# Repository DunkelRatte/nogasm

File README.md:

# Nogasm

This is a fork of the [original nogasm project](https://github.com/nogasm/nogasm).

## Hardware

### Board

Count | Name | Digikey link | Comment |
-----|--------|-------------|---------|
1 | Teensy LC | https://www.digikey.com/short/31cn1n ||
13 | WS2812b RGB LED | https://www.digikey.com/short/31c04r ||
1 | MP3V5050GP | https://www.digikey.com/short/31c04n ||
1 | PEL12T-4225S-S1024 (COM-10982 encoder, backlit) | https://www.digikey.com/short/31cn19 ||
1 | COM-10597 (encoder knob, transparent) | https://www.digikey.com/short/djdq9jpq ||
1 | MCP6001RT-I/OT | https://www.digikey.com/short/31cnvz ||
1 | CGRA4004-G | https://www.digikey.com/short/31c0mw ||
1 | BUK92150-55A | https://www.digikey.com/short/31cnvb ||
3 | MMBT2222A | https://www.digikey.com/short/bmf4f7fn ||
1 | LM7805CT/NOPB | https://www.digikey.com/short/wcn5wvbh | SMD versions more common now |
2 | 10µF 20V tantalum cap 1206 | https://www.digikey.com/short/4pf7p859 || 
15 | 1µF 16V ceramic cap 0805 | https://www.digikey.com/short/31cdcp ||
1 | 0.33µF 16V ceramic cap 0603 | https://www.digikey.com/short/31cdt4 ||
3 | 10nF 16V ceramic cap 0805| https://www.digikey.com/short/31cd7f ||
1 | 10k Ohm trimmer | https://www.digikey.com/short/31cnvv ||
1 | 15k Ohm resistor 0805 | https://www.digikey.com/short/31c04h ||
2 | 10k Ohm resistor 0805 | https://www.digikey.com/short/31cdt9 ||
2 | 750 Ohm resistor 0805 | https://www.digikey.com/short/31cdtw ||
1 | 300 Ohm resistor 0805 | https://www.digikey.com/short/31c04q ||
2 | 180 Ohm resistor 0805 | https://www.digikey.com/short/31cdtn ||
1 | 4pos DIP switch | https://www.digikey.com/short/31cn1m ||
1 | Barreljack socket 1.3mm/3.5mm | https://www.digikey.com/short/31c0mt ||
1 | Barreljack plug 1.3mm/3.5mm | https://www.digikey.com/short/31c0mj ||
1 | Barreljack socket 2.5mm/5.5mm | https://www.digikey.com/short/31c0mh ||

[You can order all of the above parts in one cart from Digikey](https://www.digikey.com/short/d32z5423)

#### Aisler Kit
[You can order PCBs and/or all parts as a single kit on Aisler](https://aisler.net/DunkelRatte/nogasm/board)

#### Power
You'll need 12V/1.5A DC power supply with a 2.5mm/5.5mm barreljack plug (or fitting to above bigger socket).

### Vibrator
The case is designed for a RS-555 motor. [Aliexpress lists several versions](https://www.aliexpress.com/wholesale?SearchText=rs555).
You'll need to press a weight onto it.

Other 12V DC toys controlable with PWM and using up to 2A should work as well.

### Plug
An inflatable buttplug is used for pressure detection. For example "*Fanny Hill*" by *Seven Creations*.

## Software

### Flashing the teensy

[Install the Teensy Loader Application](https://www.pjrc.com/teensy/loader.html).
After There are two ways to get the firmware onto the device:

#### Flashing the compiled .hex
This is the easiest way. Download the `.hex` file and use the loader to upload the file to the device.

#### Compiling the code yourself
[Download and install Teensyduino](https://www.pjrc.com/teensy/td_download.html).
Afterwards get the sourcecode, compile and upload it via the arduino IDE.

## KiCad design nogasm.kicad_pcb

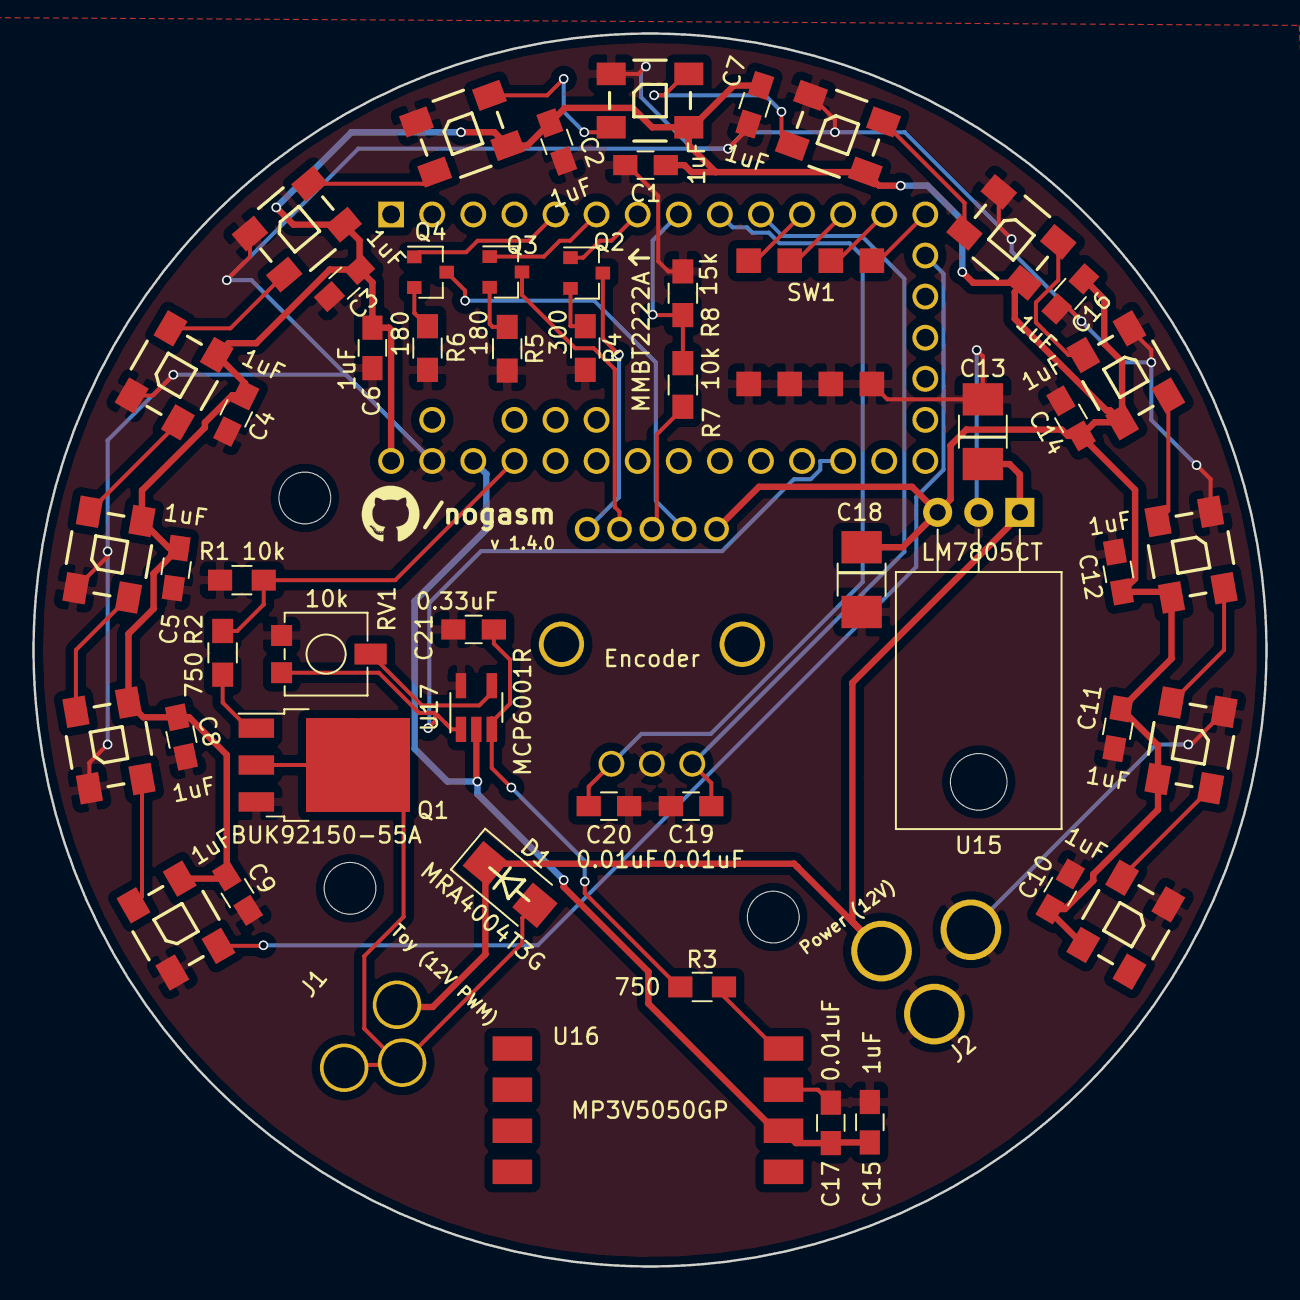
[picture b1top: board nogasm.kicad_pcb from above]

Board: 2 copper layers, 76.2 x 76.2 mm, 56 parts (1 on the bottom side), 41 nets.

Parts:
C1, C2, C3, C4, C5, C6, C7, C8, C9, C10, C11, C12, C14, C15, C16: 1uF; C_0805_HandSoldering
C13, C18: 10uF; C_1210_HandSoldering
C17, C19, C20: 0.01uF; C_0805_HandSoldering
C21: 0.33uF; C_0805_HandSoldering
D1: MRA4004T3G; D_SMA_0202
Encoder: Rotary_Encoder_Switch_RGB; COM-10982
J1: DC Jack PJ-031DH 3.5mm; Barreljack_3mm
J2: DC Jack PRT-10811; Barreljack_5.4mm
Q1: BUK92150-55A; TO-252-3_TabPin2
Q2, Q3, Q4: MMBT2222A; SOT-23
R1, R7: 10k; R_0805_HandSoldering
R2, R3: 750; R_0805_HandSoldering
R4: 300; R_0805_HandSoldering
R5, R6: 180; R_0805_HandSoldering
R8: 15k; R_0805_HandSoldering
RV1: 10k; Potentiometer_Trimmer_Vishay_TS53YL
SW1: SW_DIP_x04; SW_DIP_4_SMD
U1, U2, U3, U4, U5, U6, U7, U8, U9, U10, U11, U12, U13: WS2812B
U14: Teensy-LC; Teensy30_31_32_LC
U15: LM7805CT; TO-220_Horizontal
U16: MP3V5050GP
U17: MCP6001R; SOT-23-5_HandSoldering

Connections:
+3V3: C15.1, C17.1, U14.31, U16.2, U17.2
+5V: C1.1, C2.1, C3.1, C4.1, C5.1, C6.2, C7.1, C8.1, C9.1, C10.1, C11.1, C12.1, C14.1, C16.1, C18.1, Encoder.5, U1.1, U2.1, U3.1, U4.1, U5.1, U6.1, U7.1, U8.1, U9.1, U10.1, U11.1, U12.1, U13.1, U14.33, U15.3
+12V: C13.1, D1.1, J1.1, J2.1, U15.1
/5VIO: U1.4, U14.15
/ENC_A: C20.1, Encoder.A, U14.9
/ENC_B: C19.1, Encoder.B, U14.10
/ENC_Bl: Q4.1, U14.5
/ENC_Gr: Q3.1, U14.6
/ENC_Rd: Q2.1, U14.7
/ENC_SW: R7.2, R8.1, U14.8
/V_PRES: RV1.1, U14.22, U17.1
GND: C1.2, C2.2, C3.2, C4.2, C5.2, C6.1, C7.2, C8.2, C9.2, C10.2, C11.2, C12.2, C13.2, C14.2, C15.2, C16.2, C17.2, C18.2, C19.2, C20.2, C21.2, Encoder.C, J2.2, J2.3, Q1.3, R1.1, R4.2, R5.2, R6.2, R8.2, RV1.3, SW1.1, SW1.2, SW1.3, SW1.4, U1.3, U2.3, U3.3, U4.3, U5.3, U6.3, U7.3, U8.3, U9.3, U10.3, U11.3, U12.3, U13.3, U14.32, U15.2, U16.3, U17.5
unnamed: C21.1, R3.1, U17.3
unnamed: D1.2, J1.2, J1.3, Q1.2
unnamed: Q1.1, R2.1
unnamed: Q2.2, R4.1
unnamed: Encoder.1, Q2.3
unnamed: Q3.2, R5.1
unnamed: Encoder.2, Q3.3
unnamed: Q4.2, R6.1
unnamed: Encoder.4, Q4.3
unnamed: R1.2, R2.2, U14.30
unnamed: R3.2, U16.4
unnamed: Encoder.3, R7.1
unnamed: RV1.2, U17.4
unnamed: SW1.5, U14.14
unnamed: SW1.6, U14.13
unnamed: SW1.7, U14.12
unnamed: SW1.8, U14.11
unnamed: U1.2, U2.4
unnamed: U2.2, U3.4
unnamed: U3.2, U4.4
unnamed: U4.2, U5.4
unnamed: U5.2, U6.4
unnamed: U6.2, U7.4
unnamed: U7.2, U8.4
unnamed: U8.2, U9.4
unnamed: U10.2, U11.4
unnamed: U9.2, U10.4
unnamed: U11.2, U12.4
unnamed: U12.2, U13.4

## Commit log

2017-05-17 init
2017-05-17 Adding netlist to gitignore
2017-05-17 Squashed 'kicad-library/' content from commit fbfcf3a1
    git-subtree-dir: kicad-library
    git-subtree-split: fbfcf3a1d5e57af7e85bbe38c28fd9cc36468816
2017-05-17 initial commit with data
2017-05-18 changing DIP switch to SMD and fixing some library linking
2017-05-18 rerouting some caps to front copper
2017-05-19 refactoring
2017-05-26 adding proper barrel jack footprints and using them on the board
2017-06-01 fixing pad size of C13 and C 18. Fixing wrong D1 polarity
2017-06-01 fixing BUK pinout
2017-06-01 rerouting
2017-06-01 added bck to ignore file
2017-07-21 fixing cap polarity marking on silkscreen
2017-07-21 removing silkscreen for drillholes and increasing version number
2017-07-21 fixing wrong connected ENC_B / ENC_Bl nets
2017-07-31 fixing unconnected net and some pcb layout changes
2017-08-01 layouting LEDs with proper angular distance
2017-08-01 renaming LEDs
2017-08-06 adding readme and license files
2017-08-06 adding WIP of firmware rewrite
2017-08-06 updating readme regarding power
2017-08-06 adding board render image
2021-03-28 Support KiCAD 5.x; include gerber files
2021-03-29 Updated BoM
